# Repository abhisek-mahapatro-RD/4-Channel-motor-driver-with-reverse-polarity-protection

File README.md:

# 4-Channel DRV8871 Motor Driver

A compact **4-channel brushed DC motor driver board** based on the **TI DRV8871**, designed for controlling four independent DC motors with integrated reverse-polarity protection.

## Features

- 4 independent DC motor channels
- DRV8871-based motor control
- **2 A continuous output current per channel**
- **3.6 A peak output current per channel**
- Reverse-polarity protection
- Reverse polarity visual alert using ERR LED
- Screw terminals for motor connections
- 2.54 mm header pins for control signals
- Suitable for microcontroller-based control

## Specifications

| Parameter | Specification |
|---|---|
| Number of Channels | 4 |
| Motor Driver IC | TI DRV8871 |
| Motor Type | Brushed DC Motor |
| Continuous Current | **2 A / Channel** |
| Peak Current | **3.6 A / Channel** |
| Control Interface | 2.54 mm Header Pins |
| Motor Connection | Screw Terminals |
| Protection |PMOS Reverse-Polarity Protection |
| PCB Revision | Rev 2.0 |

## Channel Configuration

The board provides four independent motor-driver channels:

- **Channel 1 — Motor A**
- **Channel 2 — Motor B**
- **Channel 3 — Motor C**
- **Channel 4 — Motor D**

Each channel is controlled independently through the DRV8871 motor-driver circuitry.

## Applications

- Robotics
- Mobile robots
- DC motor control
- Automation systems
- Educational and development projects

## Revision History

### Rev 1.0

**Initial Release**

- Basic 4-channel DRV8871 motor driver
- 2.54 mm pins
- No additional protection 
- Four independent motor channels

### Rev 2.0

**Connectivity & Protection Upgrade**

- Added screw terminals
- Added reverse-polarity protection
- Improved ease of motor connection
- Improved protection on the power input

- ## License

This hardware design is released under the **CERN Open Hardware Licence Version 2 – Permissive (CERN-OHL-P-2.0)**.

You are free to use, study, modify, manufacture, and distribute hardware based on this design, subject to the terms and conditions of the licence.

**Copyright © 2026 Abhisek Mahapatro**

For the complete licence terms, see the [`LICENSE`](LICENSE) file.

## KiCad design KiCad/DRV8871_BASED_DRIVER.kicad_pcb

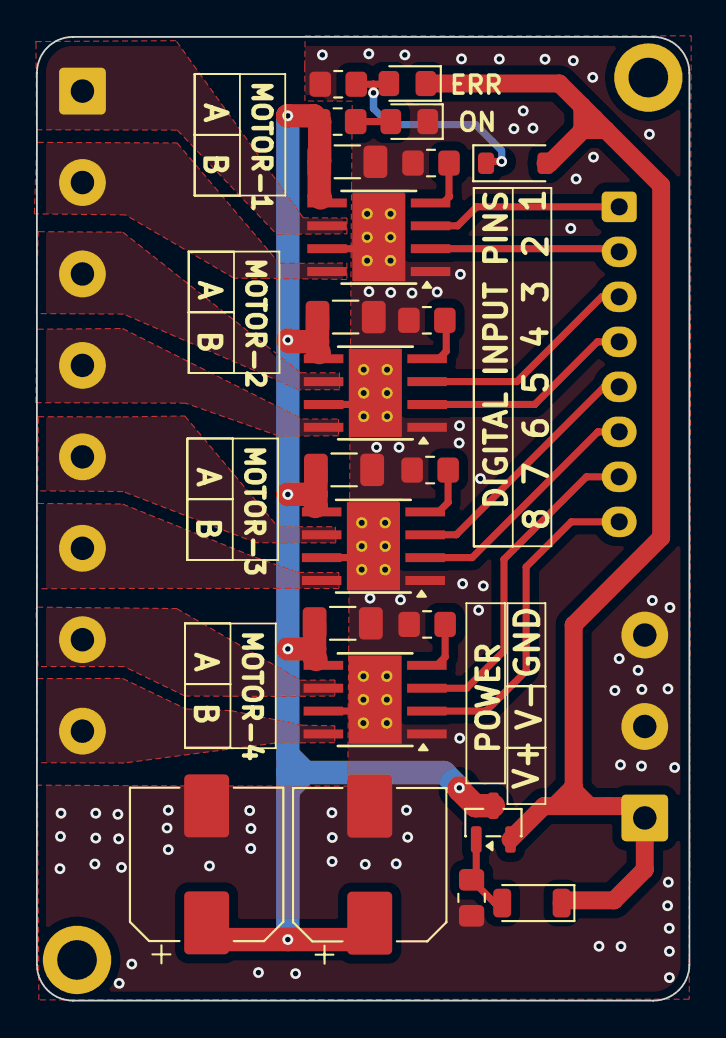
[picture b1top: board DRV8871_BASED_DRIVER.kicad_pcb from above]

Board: 2 copper layers, 36.2 x 53.5 mm, 24 parts (0 on the bottom side), 18 nets.

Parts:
C1, C2: 220uF; CP_Elec_8x10
C2#2, C3, C4, C5: 100nF; C_1206_3216Metric_Pad1.33x1.80mm_HandSolder
D2: BZT52C10; D_SOD-123
D3: ERR; LED_0805_2012Metric_Pad1.15x1.40mm_HandSolder
D4: 1N4148W; D_SOD-123
D4#2: PWR; LED_0805_2012Metric_Pad1.15x1.40mm_HandSolder
J1: Conn_01x08_Pin; JST_XA_B08B-XASK-1_1x08_P2.50mm_Vertical
J6: Conn_01x03_Pin; TerminalBlock_Phoenix_MKDS-1,5-3-5.08_1x03_P5.08mm_Horizont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
Q1: Si2371EDS; SOT-23
R1, R2, R3, R4: 30K; R_0805_2012Metric_Pad1.20x1.40mm_HandSolder
R5, R6: 1K; R_0805_2012Metric_Pad1.20x1.40mm_HandSolder
R7: 10K; R_0805_2012Metric_Pad1.20x1.40mm_HandSolder
U1, U2, U4, U4#2: DRV8871DDA; Texas_HTSOP-8-1EP_3.9x4.9mm_P1.27mm_EP2.95x4.9mm_Mask2.4x3.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

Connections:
/IN1: J1.1, U4.3 (IN1)
/IN2: J1.2, U4.2 (IN2)
/IN3: J1.3, U1.3 (IN1)
/IN4: J1.4, U1.2 (IN2)
/IN5: J1.5, U2.3 (IN1)
/IN6: J1.6, U2.2 (IN2)
/IN7: J1.7, U4#2.3 (IN1)
/IN8: J1.8, U4#2.2 (IN2)
/V+: D2.1 (K), D3.1 (K), D4.2 (A), J6.1, Q1.2 (S)
GND: C1.2, C2.2, C2#2.2, C3.2, C4.2, C5.2, D4#2.1 (K), J6.2, J6.3, R1.2, R2.2, R3.2, R4.2, R6.2, R7.2, U1.1 (GND), U1.7 (GND), U1.9 (GND), U2.1 (GND), U2.7 (GND), U2.9 (GND), U4.1 (GND), U4.7 (GND), U4.9 (GND), U4#2.1 (GND), U4#2.7 (GND), U4#2.9 (GND)
unnamed: D4#2.2 (A), R5.1
unnamed: D2.2 (A), Q1.1 (G), R7.1
unnamed: D3.2 (A), D4.1 (K), R6.1
unnamed: R2.1, U1.4 (ILIM)
unnamed: R3.1, U2.4 (ILIM)
unnamed: R4.1, U4#2.4 (ILIM)
unnamed: R1.1, U4.4 (ILIM)
VCC: C1.1, C2.1, C2#2.1, C3.1, C4.1, C5.1, Q1.3 (D), R5.2, U1.5 (VM), U2.5 (VM), U4.5 (VM), U4#2.5 (VM)
